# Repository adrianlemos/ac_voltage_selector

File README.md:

## Selecione o Idioma: | Português  | [Inglês](README_en.md) | [Espanhol](README_es.md)  |

## Observação
Este projeto apesar de possuir o README em três idiomas ele será sempre atualizado em português primeiro. 

# AC Voltage Selector

Este projeto foi criado com a intenção de selecionar automaticamente a tensão da rua ou do inversor de tensão. par amaiores informações sobre o porque do projeto vale apena visitar o [Blog](adrianlemos.com)

Uma grande observação a ser feita é que esta placa e componentes foram pensados para serem encontados no Brasil.

<!-- Table of Contents -->

<!-- End of Conttents -->
# Caixa 
- Esta placa foi criada para o Modelo: DIM FUNDO 075 da Marca: Patola.
- Botão switch [APEM 13435AD2K](https://www.mouser.com/ProductDetail/Apem/13435AD2K?qs=uQD7XCvsSCP0kwEECjH0NQ%3D%3D)

# Descrição

## Schematico

## 3D Imagens

# Começando

## Dependencias

### Programas utilizados
- Schematic and PCB Layout
  - Kicad 6.0.2

# Autor

Schematico - Adrian Lemos
Placa de Circuito Impresso - Adrian Lemos

# Licensa

Placa Open Hardware sobe a [licensa GPL-3.0](https://github.com/adrianlemos/ac_voltage_selector/blob/main/LICENSE)

# Bibliografia e links externoss

Mais informações sobre este componente do Projeto no [Blog](https://adrianlemos.com/2022/12/29/back-up-de-tensao-ac/)

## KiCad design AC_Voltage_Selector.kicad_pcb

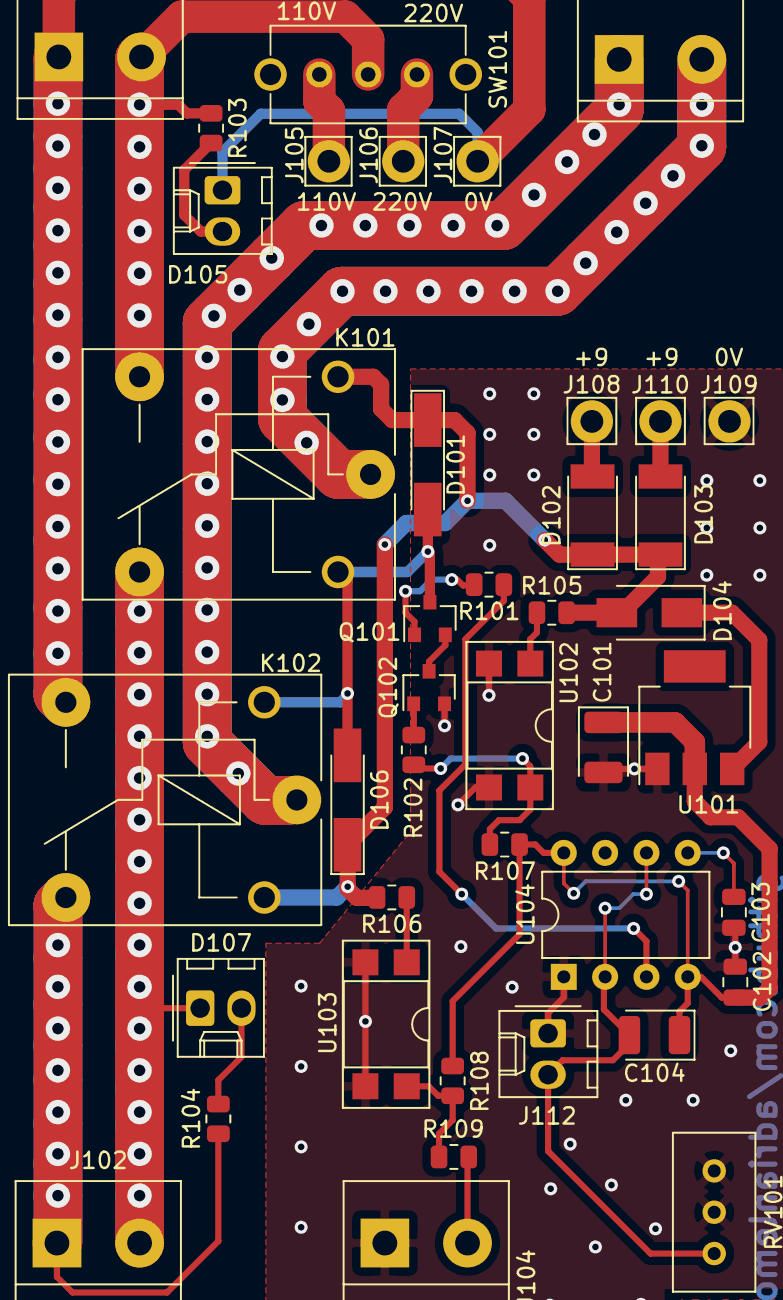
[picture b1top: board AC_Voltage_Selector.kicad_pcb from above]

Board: 2 copper layers, 42 parts (1 on the bottom side), 28 nets.

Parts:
C101: 100uF x 6.3V; CP_EIA-3528-21_Kemet-B
C102, C103: 100nF; C_0805_2012Metric
C104: 100uF x 6v3; CP_EIA-3528-21_Kemet-B
D101, D106: 1N4148; D_MiniMELF_Handsoldering
D102, D103: SM4007; D_MELF
D104: D_Schottky; D_SMA
D105, D107: LED; Molex_KK-254_AE-6410-02A_1x02_P2.54mm_Vertical
J101, J102, J103, J104: Screw_Terminal_01x02; TerminalBlock_bornier-2_P5.08mm
J105, J106, J107, J108, J109, J110: Conn_01x01; Pin_D1.4mm_L8.5mm_W2.8mm_FlatFork
J112: Conn_01x02; Molex_KK-254_AE-6410-02A_1x02_P2.54mm_Vertical
K101, K102: FINDER-36.11; Relay_SPDT_Finder_36.11
LOGO101: Logo_Open_Hardware_Small; OSHW-Symbol_13.4x12mm_SilkScreen
Q101, Q102: BC817; SOT-23
R101, R102: 2K2; R_0805_2012Metric
R103, R104: R_Small; R_0805_2012Metric
R105, R106, R107: 390R; R_0805_2012Metric
R108: 10K; R_0805_2012Metric
R109: 1K; R_0805_2012Metric
RV101: 50M; Potentiometer_Bourns_3296W_Vertical
SW101: SW_SPDT; HH_Switch
U101: LM1117-5.0; SOT-223
U102, U103: PC817; DIP-4_W7.62mm_SMDSocket_SmallPads
U104: NE555P; DIP-8_W7.62mm

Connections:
+5V: C101.1, C102.1, C104.1, R107.1, R108.1, U101.2, U104.4, U104.8
+9V: D101.1, D102.1, D103.1, D104.2, D106.1, K101.A1, K102.A2, R105.2, R106.2
/110V: J105.1, SW101.1
/220V: J106.1, SW101.3
/+9VA1: D102.2, J108.1
/+9VA2: D103.2, J110.1
/Line: J101.2, K101.14, R103.1, SW101.2
/Line_Inversor: D107.1, J102.2, K101.12
/Line_Selected: J103.2, K101.11
/Neutral_Inversor: J102.1, K102.12, R104.1
/Neutral_Selected: J103.1, K102.11
/Neutral|Line: D105.1, J101.1, J107.1, K102.14
/Relay_set: D101.2, D106.2, K101.A2, K102.A1, Q101.3
/ac_voltage_relay: R102.1, R107.2, U102.4
/ac_voltage_signal: J104.2, R109.1
/ne555_timer_drive: R101.1, U104.3
GND: C101.2, C102.2, C103.2, J104.1, J109.1, J112.1, Q102.2, RV101.2, RV101.3, U101.1, U102.2, U102.3, U103.2, U103.3, U104.1
unnamed: C103.1, U104.5
unnamed: C104.2, J112.2, RV101.1, U104.2, U104.6
unnamed: D104.1, U101.3
unnamed: D105.2, R103.2
unnamed: D107.2, R104.2
unnamed: Q101.1, R101.2
unnamed: Q101.2, Q102.3
unnamed: Q102.1, R102.2
unnamed: R105.1, U102.1
unnamed: R106.1, U103.1
unnamed: R108.2, R109.2, U103.4

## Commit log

2022-12-22 Update README.md
    [doc: Add a simple template to use in the future]
2022-12-22 Update README.md
    [doc: Add new link for template usage]
2022-12-22 [doc: Just a commit test]
    - testing the commit in github website
2022-12-24 [doc: altered the format of README text]
    - Foi adicionado as Badeiras do Brasil, Estados Unidos e Espanha
    para testar um novo formato de README.
    - Adicionado README em Espanhol
    - Adicionado README em InglÊs
2022-12-28 [files: Add schematic, PCB files and images from projects]
    - Add de first files in project git.
    - Schematic
    - PCB file
    - Image folder with 3d images.
    - Kicad project
2022-12-28 [files: Altered Schematic voltage capacitor and add image files]
    - Altered C104 voltage name.
    - Add Shematic PDF and Image.
2022-12-28 [doc: Add schematic image in README file]
    - Changed the Brazilian README file to add schematic page.
2023-01-02 [doc: Edited Pt-br README to add used prograns]
    - Add kicad program version in Pt-br Readme.
2023-01-05 [Removed duplicated files]
    - Are removed all files from old Kicad Version.
2023-01-06 [Removed Back-up Folder from Project]
    - Removed Back-up folder from git
2023-01-06 [doc: Add more information in Pt-br README]
